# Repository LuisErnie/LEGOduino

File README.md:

# LEGOduino
Arduino Mega adapter for Lego Mindstorms NXT platform designed based on the board by [Wayne and Layne](https://www.wayneandlayne.com/projects/bricktronics-megashield/) with:
- 4 Motor Ports with L298 driver
- 4 Sensor ports with interface for color and ultrasonic sensors
- External port for motors with onboard regulator
- Aditional PWM, ADC and GPIO ports brake out to interface aditional devices
- UART and I2C breakout

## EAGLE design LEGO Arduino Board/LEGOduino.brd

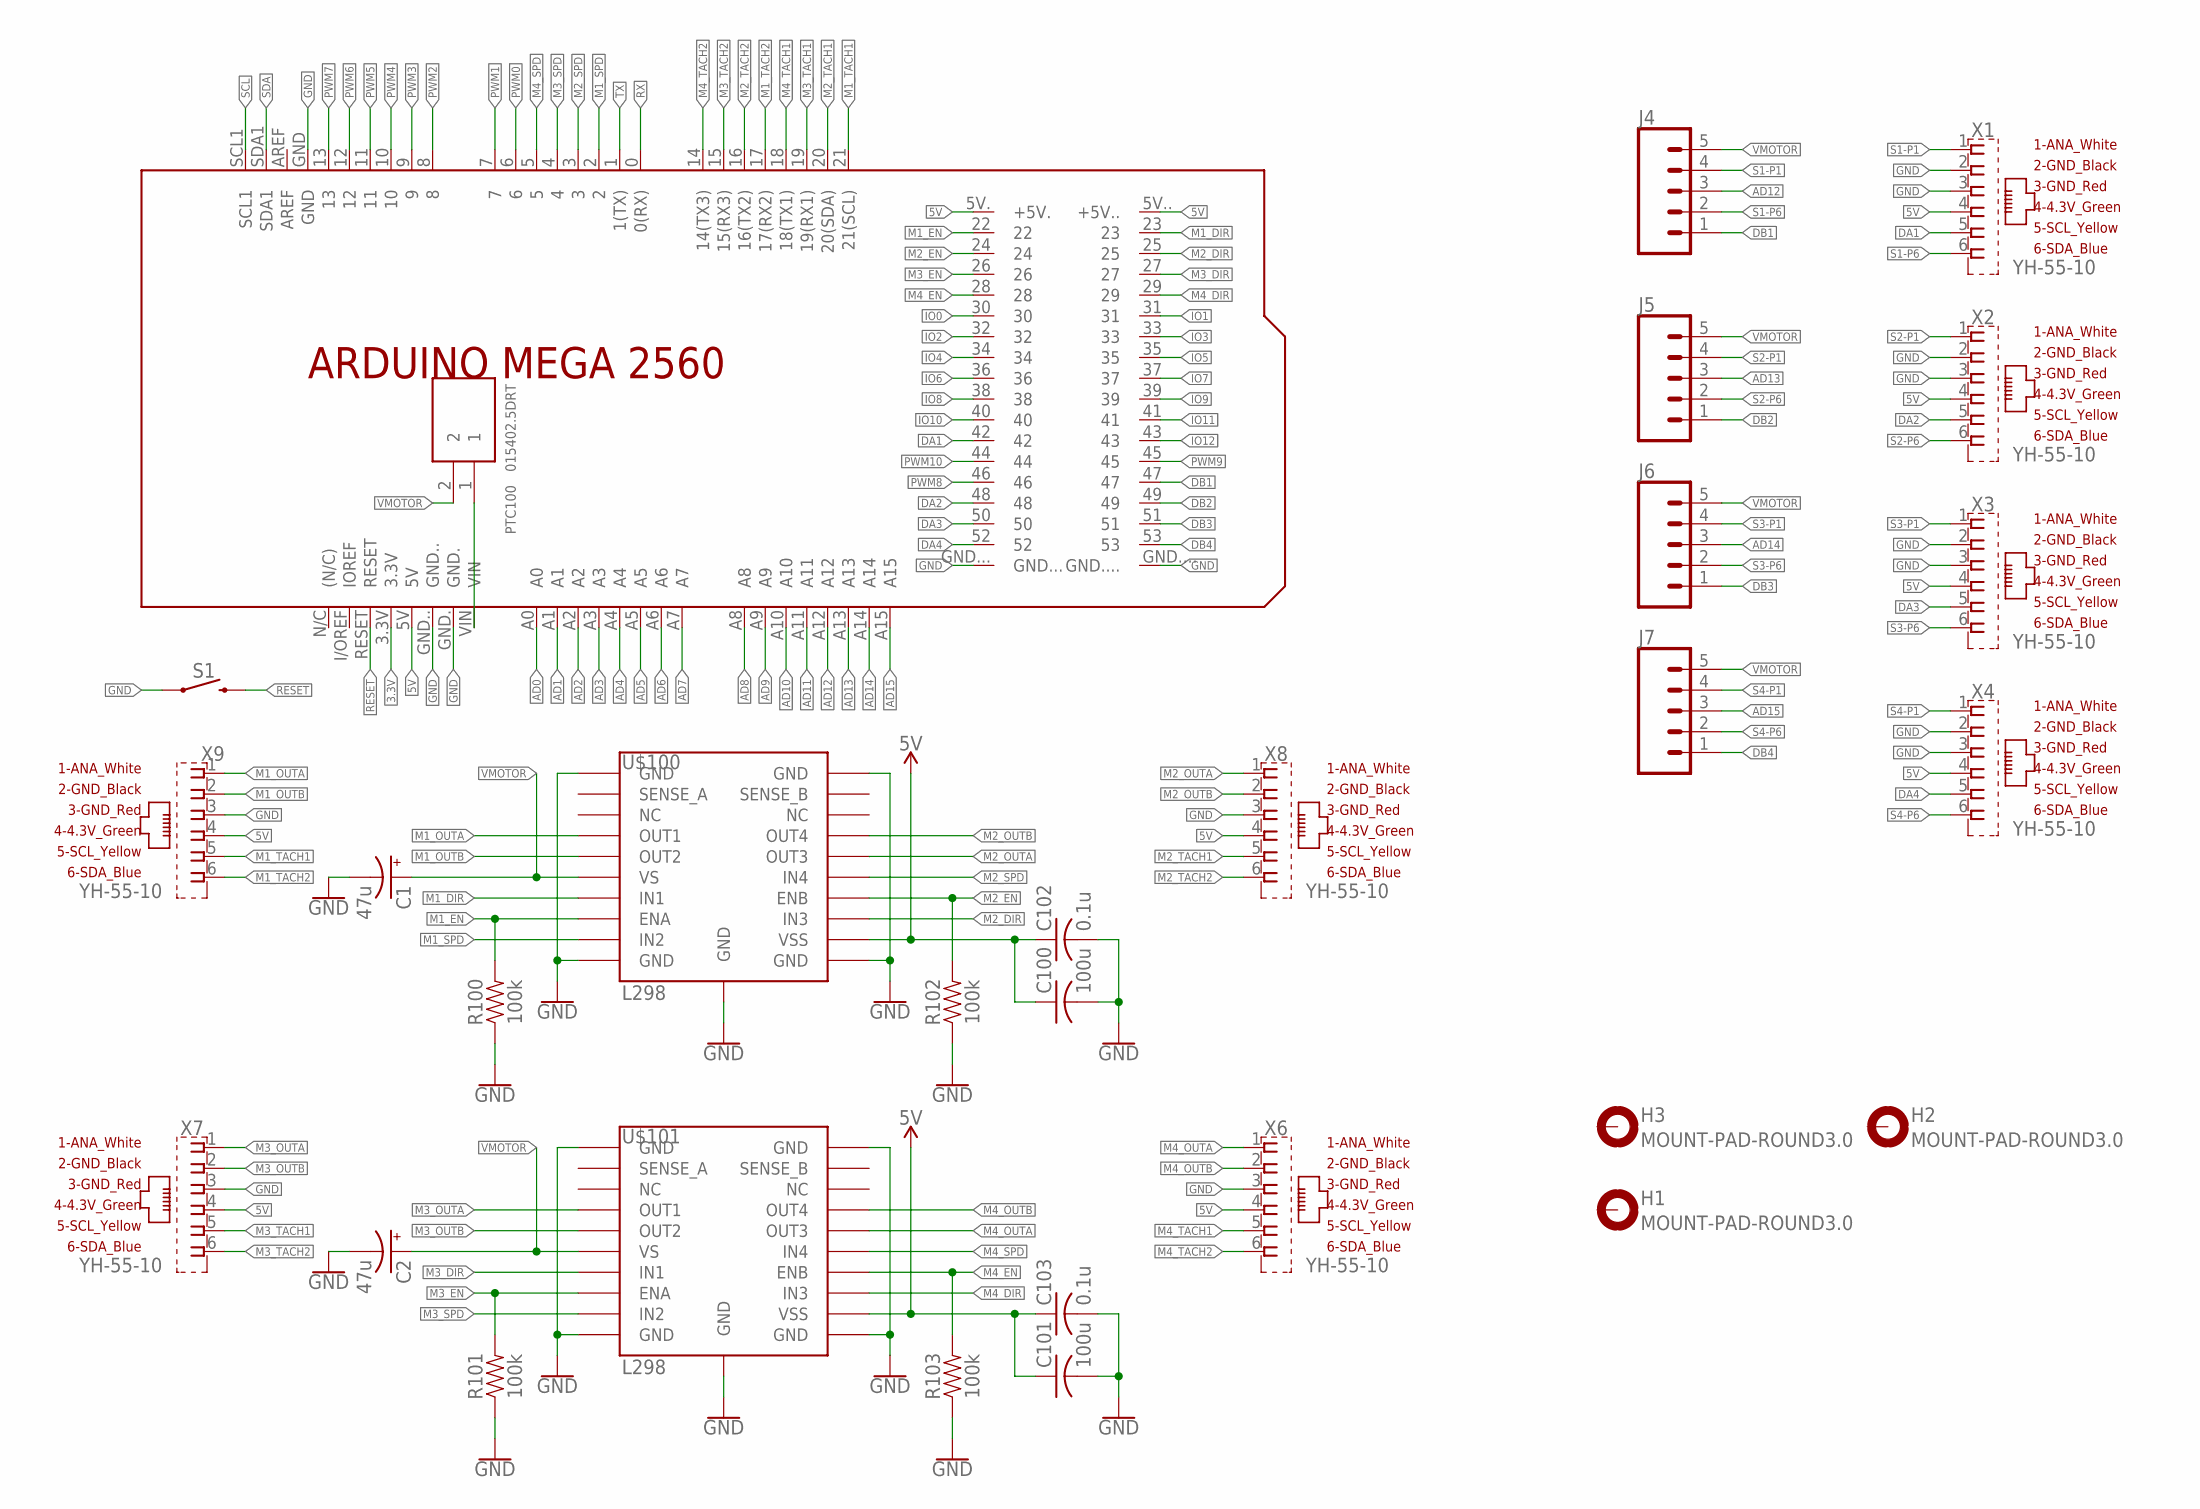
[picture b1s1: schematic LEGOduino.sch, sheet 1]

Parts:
C1, C2: 47u; CAPAE830X1050N
C100, C101: 100u; C0805K
C102, C103: 0.1u; C0805K
H1, H2, H3: MOUNT-PAD-ROUND3.0; 3,0-PAD
J4, J5, J6, J7: CONN_05; 1X05
PCB100: ARDUINO_MEGA2560
PTC100: 015402.5DRT; FUSM9750X381N
R100, R101, R102, R103: 100k; 0805
S1: MOMENTARY-SWITCH-SPST-SMD-5.2MM; TACTILE_SWITCH_SMD_5.2MM
U$100, U$101: L298; POWERSO20_L298_PAD
X1, X2, X3, X4, X6, X7, X8, X9: YH-55-10

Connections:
3.3V: PCB100.3.3V
5V: C100.1, C101.1, C102.1, C103.1, PCB100.5V, PCB100.5V. (+5V.), PCB100.5V.. (+5V..), U$100.12 (VSS), U$101.12 (VSS), X1.4 (4_4.3V_GREEN), X2.4 (4_4.3V_GREEN), X3.4 (4_4.3V_GREEN), X4.4 (4_4.3V_GREEN), X6.4 (4_4.3V_GREEN), X7.4 (4_4.3V_GREEN), X8.4 (4_4.3V_GREEN), X9.4 (4_4.3V_GREEN); also elsewhere on the board
AD0: PCB100.A0; also elsewhere on the board
AD1: PCB100.A1; also elsewhere on the board
AD2: PCB100.A2; also elsewhere on the board
AD3: PCB100.A3; also elsewhere on the board
AD4: PCB100.A4; also elsewhere on the board
AD5: PCB100.A5; also elsewhere on the board
AD6: PCB100.A6; also elsewhere on the board
AD7: PCB100.A7; also elsewhere on the board
AD8: PCB100.A8; also elsewhere on the board
AD9: PCB100.A9; also elsewhere on the board
AD10: PCB100.A10; also elsewhere on the board
AD11: PCB100.A11; also elsewhere on the board
AD12: J4.3, PCB100.A12
AD13: J5.3, PCB100.A13
AD14: J6.3, PCB100.A14
AD15: J7.3, PCB100.A15
DA1: PCB100.42, X1.5 (5_SCL_YELLOW)
DA2: PCB100.48, X2.5 (5_SCL_YELLOW)
DA3: PCB100.50, X3.5 (5_SCL_YELLOW)
DA4: PCB100.52, X4.5 (5_SCL_YELLOW)
DB1: J4.1, PCB100.47
DB2: J5.1, PCB100.49
DB3: J6.1, PCB100.51
DB4: J7.1, PCB100.53
GND: C1.2 (-), C2.2 (-), C100.2, C101.2, C102.2, C103.2, PCB100.GND, PCB100.GND., PCB100.GND.., PCB100.GND..., PCB100.GND...., R100.1, R101.1, R102.1, R103.1, S1.1, U$100.1 (GND), U$100.10 (GND), U$100.11 (GND), U$100.20 (GND), U$100.PAD (GND), U$101.1 (GND), U$101.10 (GND), U$101.11 (GND), U$101.20 (GND), U$101.PAD (GND), X1.2 (2_GND_BLACK), X1.3 (3_GND_RED), X2.2 (2_GND_BLACK), X2.3 (3_GND_RED), X3.2 (2_GND_BLACK), X3.3 (3_GND_RED), X4.2 (2_GND_BLACK), X4.3 (3_GND_RED), X6.3 (3_GND_RED), X7.3 (3_GND_RED), X8.3 (3_GND_RED), X9.3 (3_GND_RED); also elsewhere on the board
IO0: PCB100.30; also elsewhere on the board
IO1: PCB100.31; also elsewhere on the board
IO2: PCB100.32; also elsewhere on the board
IO3: PCB100.33; also elsewhere on the board
IO4: PCB100.34; also elsewhere on the board
IO5: PCB100.35; also elsewhere on the board
IO6: PCB100.36; also elsewhere on the board
IO7: PCB100.37; also elsewhere on the board
IO8: PCB100.38; also elsewhere on the board
IO9: PCB100.39; also elsewhere on the board
IO10: PCB100.40; also elsewhere on the board
IO11: PCB100.41; also elsewhere on the board
IO12: PCB100.43; also elsewhere on the board
M1_DIR: PCB100.23, U$100.7 (IN1)
M1_EN: PCB100.22, R100.2, U$100.8 (ENA)
M1_OUTA: U$100.4 (OUT1), X9.1 (1_ANA_WHITE)
M1_OUTB: U$100.5 (OUT2), X9.2 (2_GND_BLACK)
M1_SPD: PCB100.2, U$100.9 (IN2)
M1_TACH1: PCB100.21 (21(SCL)), X9.5 (5_SCL_YELLOW)
M1_TACH2: PCB100.17 (17(RX2)), X9.6 (6_SDA_BLUE)
M2_DIR: PCB100.25, U$100.13 (IN3)
M2_EN: PCB100.24, R102.2, U$100.14 (ENB)
M2_OUTA: U$100.16 (OUT3), X8.1 (1_ANA_WHITE)
M2_OUTB: U$100.17 (OUT4), X8.2 (2_GND_BLACK)
M2_SPD: PCB100.3, U$100.15 (IN4)
M2_TACH1: PCB100.20 (20(SDA)), X8.5 (5_SCL_YELLOW)
M2_TACH2: PCB100.16 (16(TX2)), X8.6 (6_SDA_BLUE)
M3_DIR: PCB100.27, U$101.7 (IN1)
M3_EN: PCB100.26, R101.2, U$101.8 (ENA)
M3_OUTA: U$101.4 (OUT1), X7.1 (1_ANA_WHITE)
M3_OUTB: U$101.5 (OUT2), X7.2 (2_GND_BLACK)
M3_SPD: PCB100.4, U$101.9 (IN2)
M3_TACH1: PCB100.19 (19(RX1)), X7.5 (5_SCL_YELLOW)
M3_TACH2: PCB100.15 (15(RX3)), X7.6 (6_SDA_BLUE)
M4_DIR: PCB100.29, U$101.13 (IN3)
M4_EN: PCB100.28, R103.2, U$101.14 (ENB)
M4_OUTA: U$101.16 (OUT3), X6.1 (1_ANA_WHITE)
M4_OUTB: U$101.17 (OUT4), X6.2 (2_GND_BLACK)
M4_SPD: PCB100.5, U$101.15 (IN4)
M4_TACH1: PCB100.18 (18(TX1)), X6.5 (5_SCL_YELLOW)
M4_TACH2: PCB100.14 (14(TX3)), X6.6 (6_SDA_BLUE)
unnamed: PCB100.VIN, PTC100.1
PWM0: PCB100.6; also elsewhere on the board
PWM1: PCB100.7; also elsewhere on the board
PWM2: PCB100.8; also elsewhere on the board
PWM3: PCB100.9; also elsewhere on the board
PWM4: PCB100.10; also elsewhere on the board
PWM5: PCB100.11; also elsewhere on the board
PWM6: PCB100.12; also elsewhere on the board
PWM7: PCB100.13; also elsewhere on the board
PWM8: PCB100.46; also elsewhere on the board
PWM9: PCB100.45; also elsewhere on the board
PWM10: PCB100.44; also elsewhere on the board
RESET: PCB100.RESET, S1.3 (2)
RX: PCB100.0 (0(RX)); also elsewhere on the board
S1-P1: J4.4, X1.1 (1_ANA_WHITE)
S1-P6: J4.2, X1.6 (6_SDA_BLUE)
S2-P1: J5.4, X2.1 (1_ANA_WHITE)
S2-P6: J5.2, X2.6 (6_SDA_BLUE)
S3-P1: J6.4, X3.1 (1_ANA_WHITE)
S3-P6: J6.2, X3.6 (6_SDA_BLUE)
S4-P1: J7.4, X4.1 (1_ANA_WHITE)
S4-P6: J7.2, X4.6 (6_SDA_BLUE)
SCL: PCB100.SCL1; also elsewhere on the board
SDA: PCB100.SDA1; also elsewhere on the board
TX: PCB100.1 (1(TX)); also elsewhere on the board
VMOTOR: C1.1 (+), C2.1 (+), J4.5, J5.5, J6.5, J7.5, PTC100.2, U$100.6 (VS), U$101.6 (VS); also elsewhere on the board

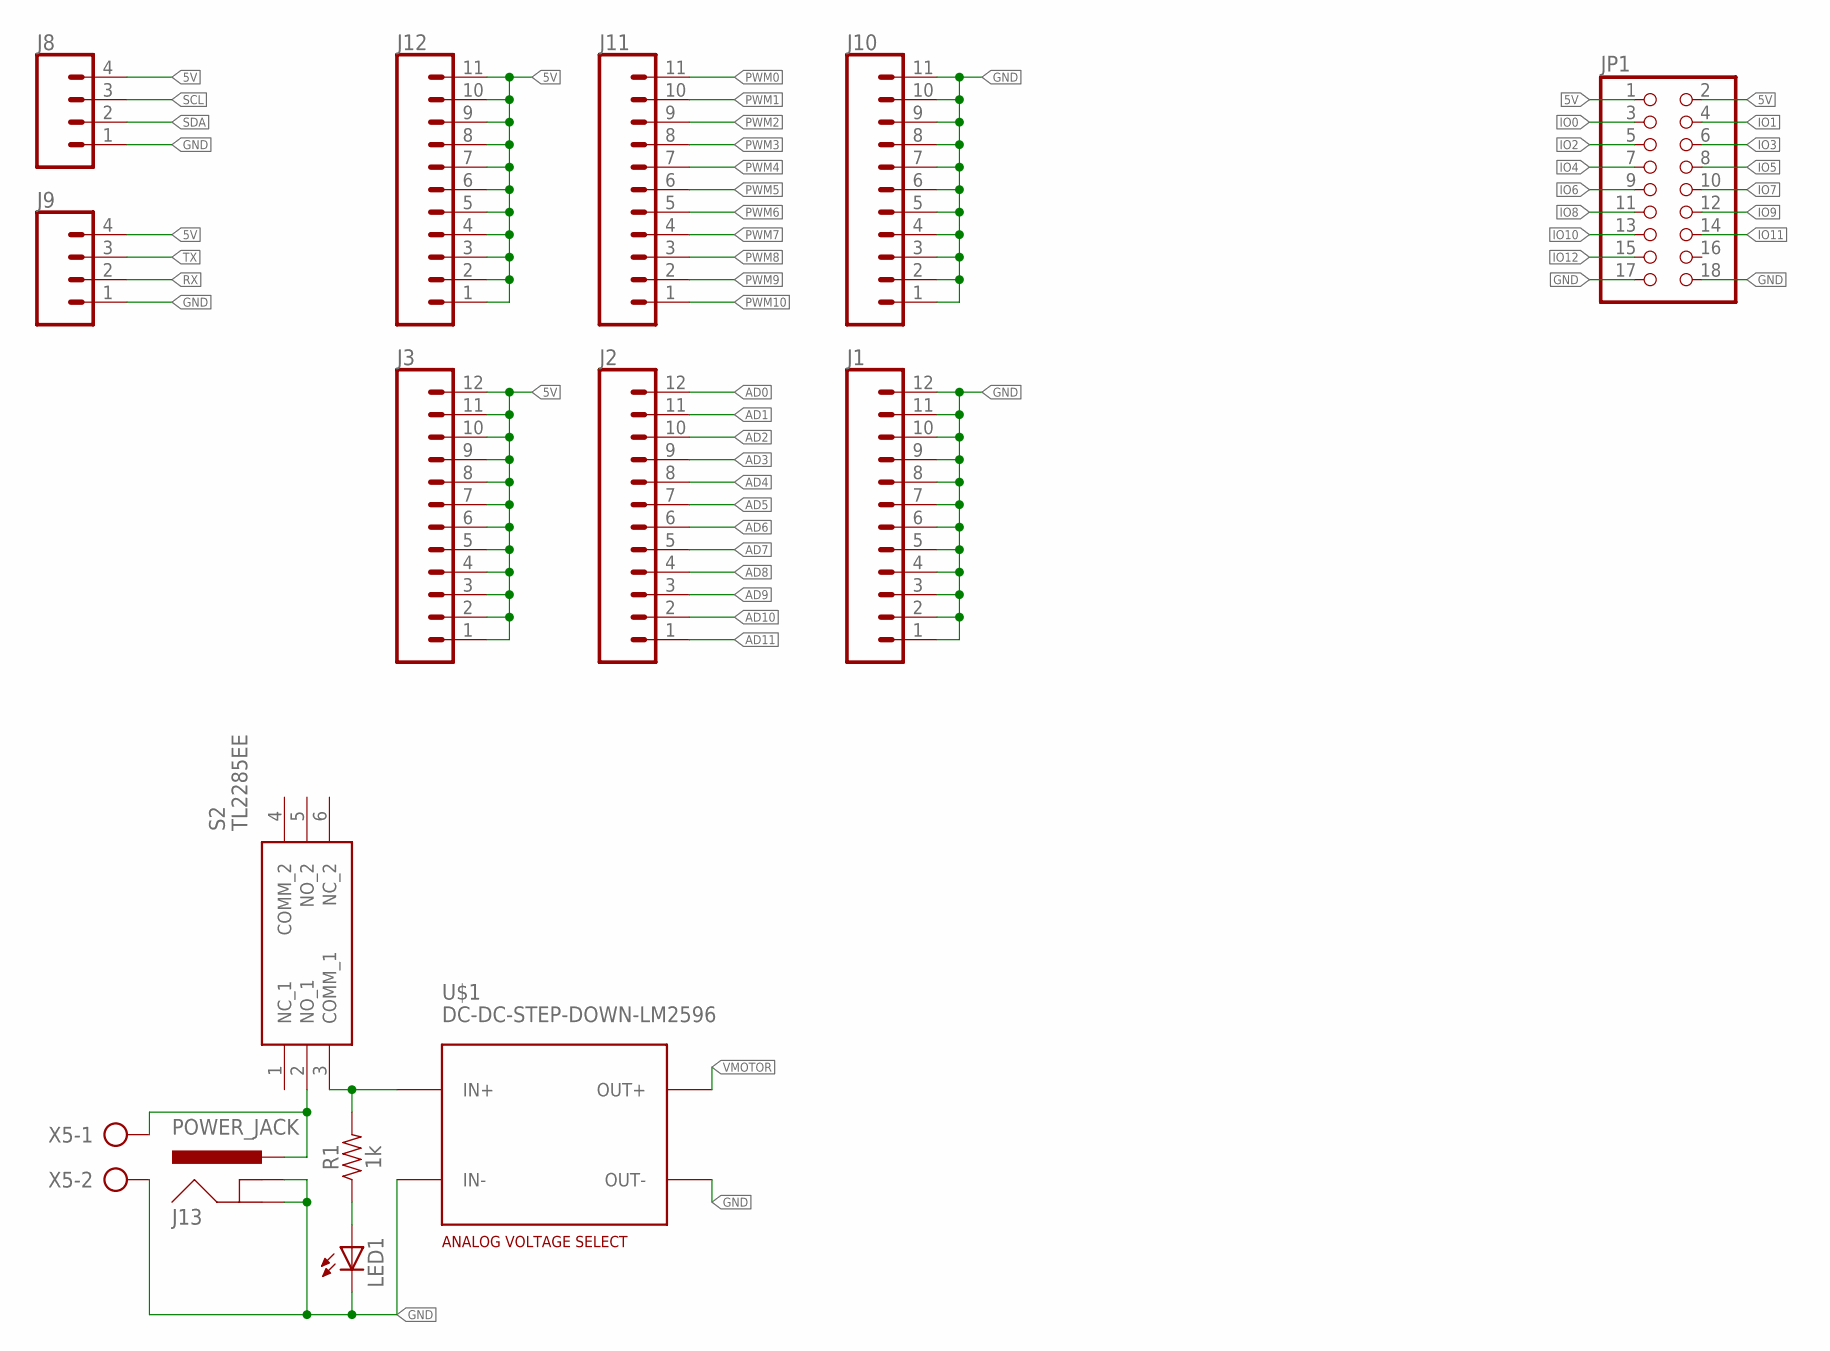
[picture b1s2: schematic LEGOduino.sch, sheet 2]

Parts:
J1, J2, J3: CONN_12; 1X12
J8, J9: CONN_04; 1X04
J10, J11, J12: CONN_11; 1X11
J13: POWER_JACK; POWER_JACK_PTH
JP1: PINHD-2X9; 2X09
LED1: LEDCHIP-LED0805; CHIP-LED0805
R1: 1k; 0805
S2: TL2285EE
U$1: DC-DC-STEP-DOWN-LM2596
X5: AK500/2-H

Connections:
5V: J3.1, J3.2, J3.3, J3.4, J3.5, J3.6, J3.7, J3.8, J3.9, J3.10, J3.11, J3.12, J8.4, J9.4, J12.1, J12.2, J12.3, J12.4, J12.5, J12.6, J12.7, J12.8, J12.9, J12.10, J12.11, JP1.1, JP1.2; also elsewhere on the board
AD0: J2.12; also elsewhere on the board
AD1: J2.11; also elsewhere on the board
AD2: J2.10; also elsewhere on the board
AD3: J2.9; also elsewhere on the board
AD4: J2.8; also elsewhere on the board
AD5: J2.7; also elsewhere on the board
AD6: J2.6; also elsewhere on the board
AD7: J2.5; also elsewhere on the board
AD8: J2.4; also elsewhere on the board
AD9: J2.3; also elsewhere on the board
AD10: J2.2; also elsewhere on the board
AD11: J2.1; also elsewhere on the board
GND: J1.1, J1.2, J1.3, J1.4, J1.5, J1.6, J1.7, J1.8, J1.9, J1.10, J1.11, J1.12, J8.1, J9.1, J10.1, J10.2, J10.3, J10.4, J10.5, J10.6, J10.7, J10.8, J10.9, J10.10, J10.11, J13.GND, J13.GNDBREAK, JP1.17, JP1.18, LED1.C, U$1.IN-, U$1.OUT-, X5.2; also elsewhere on the board
IO0: JP1.3; also elsewhere on the board
IO1: JP1.4; also elsewhere on the board
IO2: JP1.5; also elsewhere on the board
IO3: JP1.6; also elsewhere on the board
IO4: JP1.7; also elsewhere on the board
IO5: JP1.8; also elsewhere on the board
IO6: JP1.9; also elsewhere on the board
IO7: JP1.10; also elsewhere on the board
IO8: JP1.11; also elsewhere on the board
IO9: JP1.12; also elsewhere on the board
IO10: JP1.13; also elsewhere on the board
IO11: JP1.14; also elsewhere on the board
IO12: JP1.15; also elsewhere on the board
unnamed: R1.2, S2.3 (COMM_1), U$1.IN+
unnamed: LED1.A, R1.1
unnamed: J13.PWR, S2.2 (NO_1), X5.1
PWM0: J11.11; also elsewhere on the board
PWM1: J11.10; also elsewhere on the board
PWM2: J11.9; also elsewhere on the board
PWM3: J11.8; also elsewhere on the board
PWM4: J11.7; also elsewhere on the board
PWM5: J11.6; also elsewhere on the board
PWM6: J11.5; also elsewhere on the board
PWM7: J11.4; also elsewhere on the board
PWM8: J11.3; also elsewhere on the board
PWM9: J11.2; also elsewhere on the board
PWM10: J11.1; also elsewhere on the board
RX: J9.2; also elsewhere on the board
SCL: J8.3; also elsewhere on the board
SDA: J8.2; also elsewhere on the board
TX: J9.3; also elsewhere on the board
VMOTOR: U$1.OUT+; also elsewhere on the board

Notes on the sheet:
ANALOG VOLTAGE SELECT

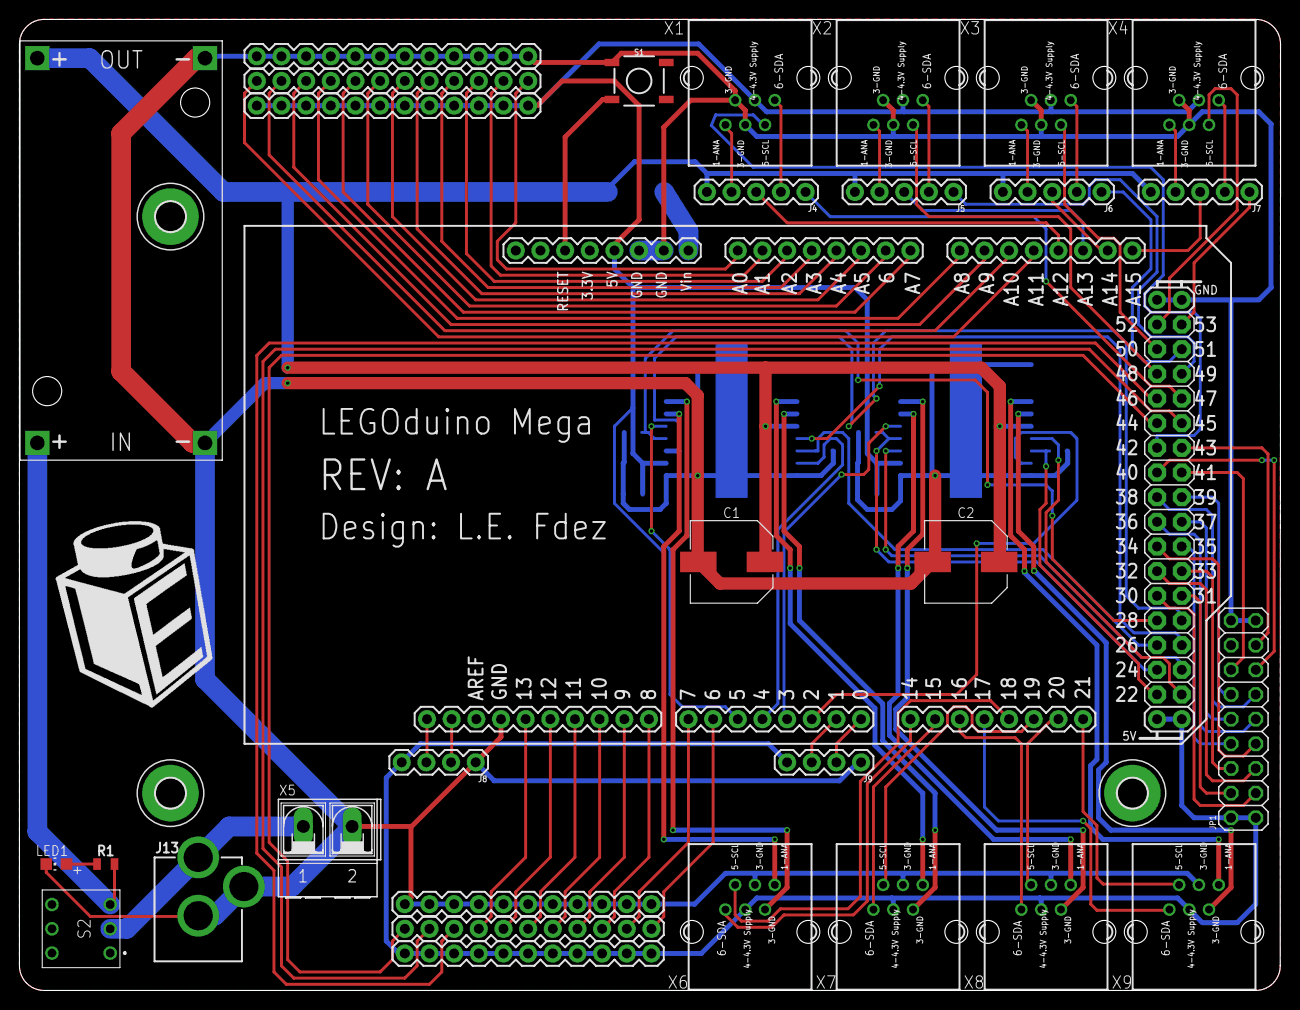
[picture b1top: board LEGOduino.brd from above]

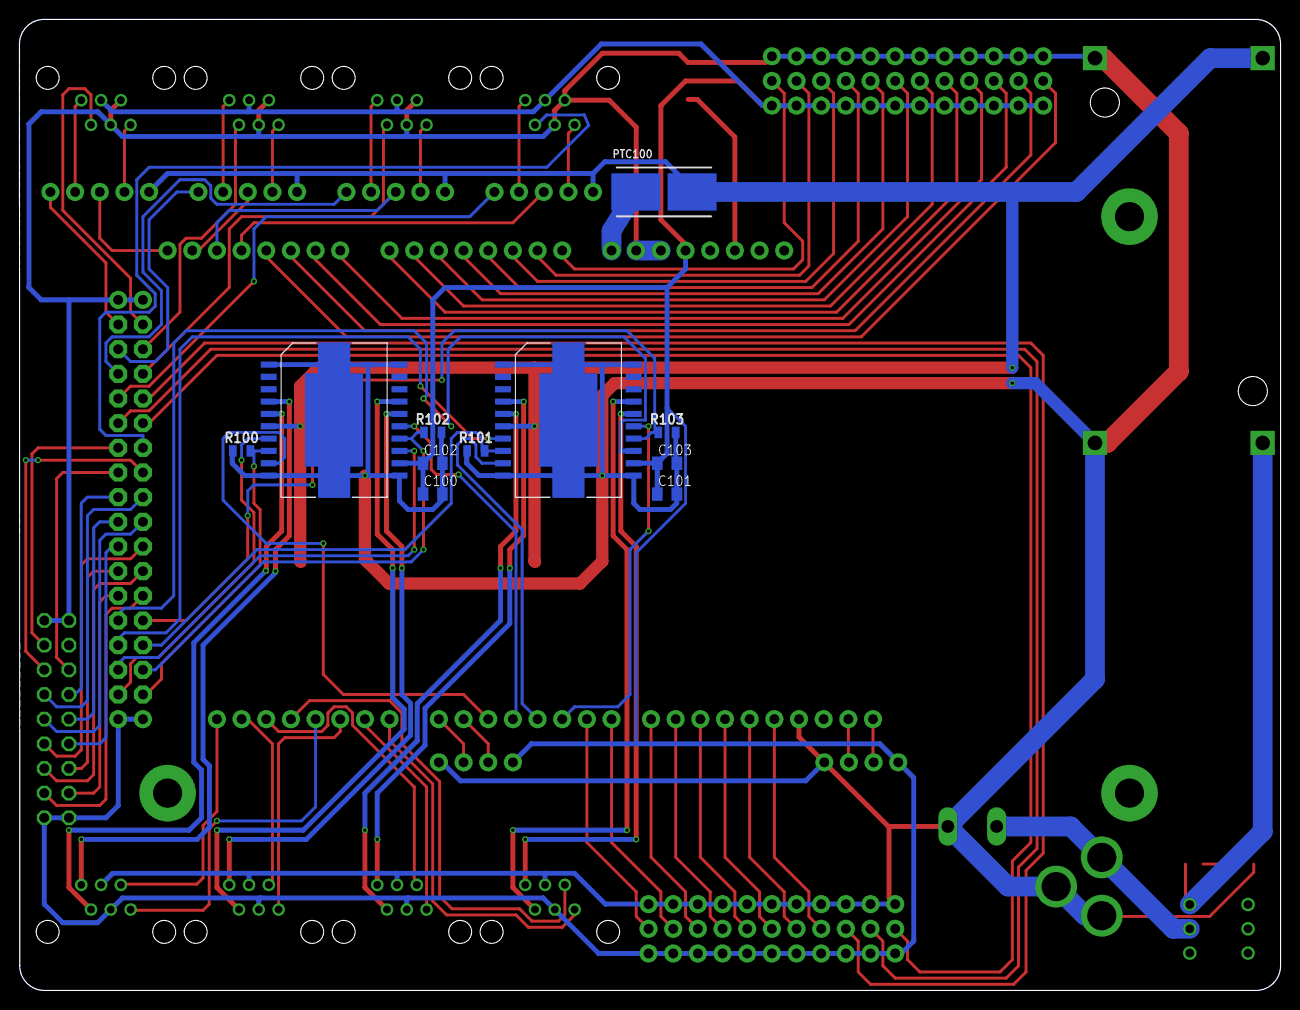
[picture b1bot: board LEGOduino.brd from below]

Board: 2 copper layers, 129.9 x 100.0 mm, 45 parts (12 on the bottom side), 96 nets.

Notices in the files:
parts and their libraries:
SparkFun-IC-Special-Function: Licensing: Creative Commons ShareAlike 4.0 International - https://creativecommons.org/licenses/by-sa/4.0
diy-modules: Released under the Creative Commons Attribution 4.0 International License: http://creativecommons.org/licenses/by/4.0
